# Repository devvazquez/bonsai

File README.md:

The main repository containing all the files involved in the creation of this smart device, such as cad files, code, designs...

## Motivation for the project
I've always wanted to do a hardware project like this, involving a camera. And I love the idea of being able to connect AI with real-world data, so this project is perfect!

## Repository Structure

```
Bonsai-Glasses/
├── bom.csv             # The bill of materials with links.
├── src/
│   ├── firmware/       # Embedded / microcontroller source code
├── hardware/
│   ├── cad/            # 3D CAD models and mechanical designs
│   └── bonsai_pcb/     # PCB schematics and board layouts
└── assets/             # Images, logos, and other design assets
```

## How it works (WIP)
Thanks to the [backend](https://github.com/devvazquez/bonsai-backend), Bonsai is able to interact easily with **free and fast** AI providers, such as Groq (for the STT and vision LLM). For TTS, it uses Piper (locally), which is esential for **Catalan** support. 
Thanks to the board, a XIAO ESP32 Sense, we can use the provided camera to give the model visual context, which is then used to describe the current enviroment.
Using the built-in web server in the firmware, you can configre all the Wifi networks, and default user button actions. You can also change parameters such as default language. Some of these parameters can also be configured using the wake word (ex. "Hey Bonsai, change the language to Spanish"). 

## Flashing a board
The [web flasher](https://devvazquez.github.io/bonsai/) writes a firmware release to a board over USB from the browser, with no toolchain to install. Plug the board in, pick a version and press write. It needs Chrome, Edge or Opera on a computer, since it runs on the Web Serial API.

Releases are cut by hand: run the **Build and publish firmware** workflow from the Actions tab, give it a version like `v1.0.0`, and it builds the firmware, tags the commit and publishes the release the page reads (`.github/workflows/release.yml`). The page itself lives in [`docs/`](docs/) and is described in [`docs/README.md`](docs/README.md).

Your settings are safe across a flash: `/config.json`, the saved networks and the voice clips are on the SD card, and only the firmware images get replaced.

## Bill of Materials
| Name | Purpose | Quantity | Total Cost (USD) | Link | Distributor |
| --- | --- | --- | --- | --- | --- |
| 3.7V Lipo Battery | Powering the device. | | $10.50 | [Buy](https://www.aliexpress.us/item/3256808990377891.html) | Aliexpress |
| JST PH 2.0 Connector | Connect battery to PCB (Bent pin socket, 2P) | | $1.95 | [Buy](https://www.aliexpress.us/item/3256807255498839.html) | Aliexpress |
| Seeed Studio XIAO ESP32S3 Sense | Tiny devboard with camera support (ESP32S3 Sense Module) | | $20.00 | [Buy](https://es.aliexpress.com/item/1005005544221475.html) | Aliexpress |
| MAX98357A I2S Audio Amplifier | Drives the speakers since ESP32 lacks enough power directly | | $1.68 | [Buy](https://www.aliexpress.us/item/3256812158409627.html) | Aliexpress |
| 75MM OV3660 120° Camera | Captures image for ESP32 to process (120 Degrees GOOD) | | $6.89 | [Buy](https://es.aliexpress.com/item/1005009339247009.html) | Aliexpress |
| Push Button | Taking the photo | | 2.95$ | [Buy](https://www.aliexpress.us/item/3256804762387991.html) | Aliexpress |
| Small Speaker | Playing the TTS sound | | 4.53$ | [Buy](https://www.aliexpress.us/item/3256811556916339.html) | Aliexpress |
| PCB | Holding all the components together | | 23$ | [Buy](https://jlcpcb.com/) | JLPCB |

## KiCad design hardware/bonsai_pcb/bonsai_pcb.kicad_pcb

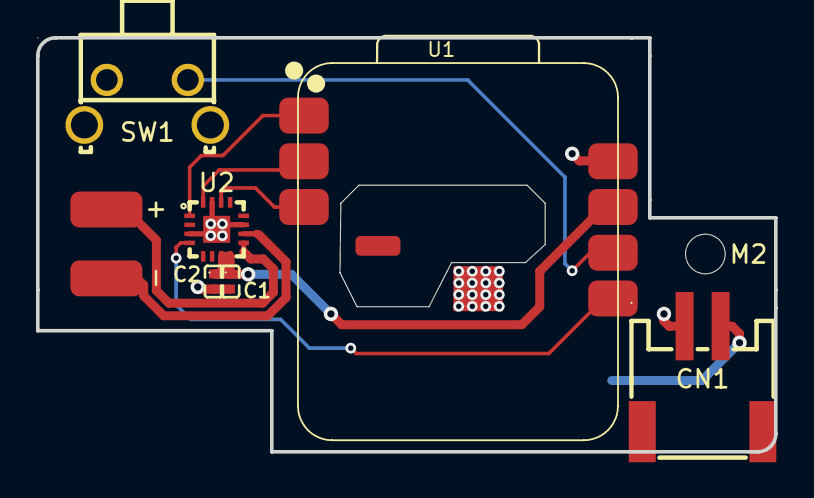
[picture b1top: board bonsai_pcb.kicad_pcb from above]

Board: 2 copper layers, 41.0 x 23.0 mm, 10 parts (1 on the bottom side), 10 nets.

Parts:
+: Conn_01x01_Socket; SolderWirePad_1x01_SMD_2x4mm
-: Conn_01x01_Socket; SolderWirePad_1x01_SMD_2x4mm
C1: 10uF; C0402
C2: 100nF; C0402
CN1: S2B-PH-SM4-TB; CONN-SMD_P2.00_S2B-PH-SM4-TB-LF-SN
J1: B+ Solder Pad; SolderWirePad_1x01_SMD_2x4mm
M2: MountingHole_2.2mm_M2
SW1: TS-1102N-5516; SW-TH_TS-1102N-5516
U1: XIAO-ESP32-S3-SMD
U2: MAX98357AETE+T; TQFN-16_L3.0-W3.0-P0.50-BL-EP1.5

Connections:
/BAT +: CN1.2, J1.1 (Pin_1_1)
/OUTN: -.1 (Pin_1_1), U2.10 (OUTN)
/OUTP: +.1 (Pin_1_1), U2.9 (OUTP)
BLCK: U1.2 (GPIO2_A1_D1), U2.16 (BCLK)
BT1: SW1.1, U1.11 (GPIO9_A10_D10_MOSI)
DIN: U1.1 (GPIO1_A0_D0), U2.1 (DIN)
GND: C1.2, C2.2, CN1.1, SW1.2, U1.13 (GND), U1.25 (GPIO40_MTDO), U2.3 (GND), U2.11 (GND), U2.15 (GND), U2.17 (EP)
LRC: U1.3 (GPIO3_A2_D2), U2.14 (LRCLK)
SD: U1.10 (GPIO8_A9_D9_MISO), U2.4 (~SD_MODE)
VIN: C1.1, C2.1, U1.12 (3V3), U2.7 (VDD), U2.8 (VDD)

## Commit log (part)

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2026-06-20 Rename pcb directory to bonsai_pcb
2026-06-20 Update project structure in README
    Removed sections for documentation, tests, and scripts from the project structure.
2026-06-20 Fix formatting in README.md for bonsai_pcb section
2026-06-21 Added the first version of the 3d case model.
2026-06-21 Update README to include bom.csv description
    Added a description for the bill of materials file.
2026-06-22 Uploaded the bom.csv
2026-06-22 Add Bill of Materials to README
    Added a Bill of Materials section with components, purposes, quantities, costs, and links.
2026-06-22 Added cart image.
2026-06-22 Rename image.png to cart-image.png
2026-06-22 Add cart image to README
    Added cart image to README for visual reference.
2026-06-29 Update README with image and structure details
    Added an image and repository structure section to README.
2026-06-29 Add image to README for smart glasses project
    Added an image to the README for visual reference.
2026-06-29 Rename project in README
    Updated project name from 'Bonsai-Glasses' to 'Bonsai'.
2026-06-29 Started working on the frimware and edited the cad file
2026-06-29 Add .env to .gitignore and update rules
